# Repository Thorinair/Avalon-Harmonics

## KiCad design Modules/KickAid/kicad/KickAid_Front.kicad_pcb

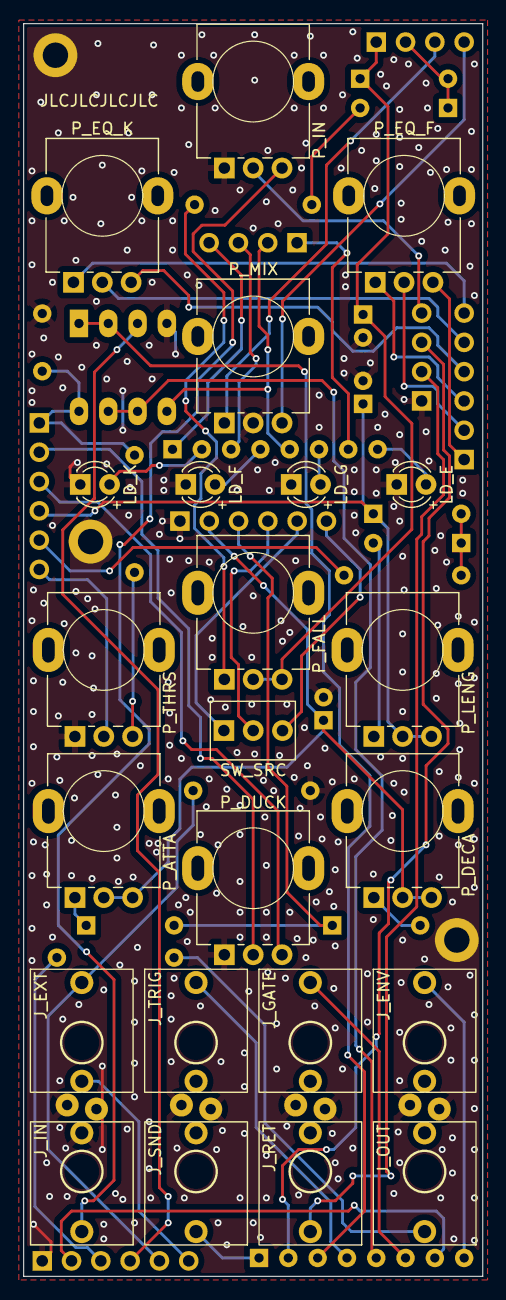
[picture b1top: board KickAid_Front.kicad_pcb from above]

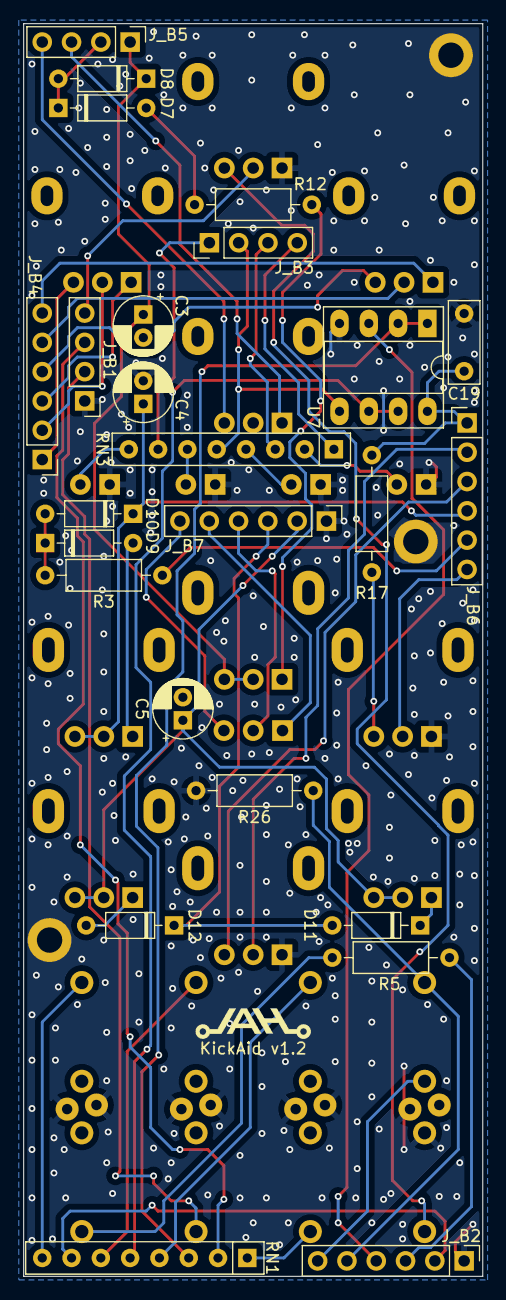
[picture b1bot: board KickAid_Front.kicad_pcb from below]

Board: 2 copper layers, 39.8 x 108.6 mm, 48 parts (25 on the bottom side), 53 nets.

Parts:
C3, C4, C5: 10uF; CP_Radial_D5.0mm_P2.00mm
C19: 0.1uF; C_Disc_D7.0mm_W2.5mm_P5.00mm
D7, D8, D9, D10, D11, D12: 1N4148; D_DO-35_SOD27_P7.62mm_Horizontal
J_B1, J_B3, J_B5: Conn_01x04_Female; PinHeader_1x04_P2.54mm_Vertical
J_B2, J_B4, J_B6, J_B7: Conn_01x06_Female; PinHeader_1x06_P2.54mm_Vertical
J_ENV: PJ301M-12; PJ301M-12 Offset
J_EXT: PJ301M-12; PJ301M-12 Offset
J_GATE: PJ301M-12; PJ301M-12 Offset
J_IN: PJ301M-12; PJ301M-12 Offset
J_OUT: PJ301M-12; PJ301M-12 Offset
J_RET: PJ301M-12; PJ301M-12 Offset
J_SND: PJ301M-12; PJ301M-12 Offset
J_TRIG: PJ301M-12; PJ301M-12 Offset
LD_E: LED; LED_D3.0mm_FlatTop
LD_F: LED; LED_D3.0mm_FlatTop
LD_G: LED; LED_D3.0mm_FlatTop
LD_K: LED; LED_D3.0mm_FlatTop
P_ATTA: A25k; Potentiometer Song Huei 9mm Trimmer
P_DECA: A250k; Potentiometer Song Huei 9mm Trimmer
P_DUCK: B100k; Potentiometer Song Huei 9mm Trimmer
P_EQ_F: B100k; Potentiometer Alpha RD901F-40-00D
P_EQ_K: B100k; Potentiometer Alpha RD901F-40-00D
P_FALL: A1M; Potentiometer Song Huei 9mm Trimmer
P_IN: A100k; Potentiometer Alpha RD901F-40-00D
P_LENG: A100k; Potentiometer Song Huei 9mm Trimmer
P_MIX: B100k; Potentiometer Alpha RD901F-40-00D
P_THRS: B100k; Potentiometer Song Huei 9mm Trimmer
R3: 220; R_Axial_DIN0207_L6.3mm_D2.5mm_P10.16mm_Horizontal
R5: 1k; R_Axial_DIN0207_L6.3mm_D2.5mm_P10.16mm_Horizontal
R12: 10k; R_Axial_DIN0207_L6.3mm_D2.5mm_P10.16mm_Horizontal
R17: 33k; R_Axial_DIN0207_L6.3mm_D2.5mm_P10.16mm_Horizontal
R26: 100k; R_Axial_DIN0207_L6.3mm_D2.5mm_P10.16mm_Horizontal
RN1: 1k; R_Array_SIP8
RN3: 10k; R_Array_SIP8
SW_SRC: SW_SPDT; SPDT
U7: LM358; DIP-8_W7.62mm_Socket_LongPads

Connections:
+12V: C19.1, J_B6.1, R17.1, U7.8 (V+)
/GATE_O1: J_B3.2, RN3.5 (R3.1), U7.5 (+)
/GATE_O2: RN1.5 (R3.1), U7.6 (-), U7.7
/OUT: J_B2.3, R5.2
/TRIG_O1: J_B2.4, U7.3 (+)
/TRIG_O2: RN1.3 (R2.1), U7.1, U7.2 (-)
GND: C3.2, C4.2, C5.2, C19.2, J_B1.1, J_B2.1, J_B7.1, J_ENV.GND, J_EXT.GND, J_GATE.GND, J_IN.GND, J_IN.SW, J_OUT.GND, J_RET.GND, J_SND.GND, J_TRIG.GND, LD_E.1 (K), LD_F.1 (K), LD_G.1 (K), LD_K.1 (K), P_DUCK.1, P_IN.1, P_MIX.2, P_THRS.1, R26.2, U7.4 (V-)
unnamed: D7.2 (A), R12.2
unnamed: D7.1 (K), D8.2 (A), J_B5.2
unnamed: C3.1, D8.1 (K), J_B5.1, P_FALL.2, P_FALL.3
unnamed: D9.2 (A), P_LENG.1
unnamed: D9.1 (K), D10.2 (A), R3.1
unnamed: C4.1, D10.1 (K), J_B6.4, P_LENG.2, P_LENG.3
unnamed: D11.2 (A), D12.1 (K), J_B7.3
unnamed: D11.1 (K), P_ATTA.1
unnamed: D12.2 (A), P_DECA.1
unnamed: J_B1.2, J_RET.SIG
unnamed: J_B1.3, RN1.2 (R1.2)
unnamed: J_B1.4, P_IN.2
unnamed: J_B2.2, RN1.7 (R4.1)
unnamed: J_B2.5, J_EXT.SIG, R26.1
unnamed: J_B2.6, J_EXT.SW
unnamed: J_B3.1, RN3.7 (R4.1)
unnamed: J_B3.3, RN3.3 (R2.1)
unnamed: J_B3.4, RN3.1 (R1.1)
unnamed: J_B4.1, P_EQ_F.3
unnamed: J_B4.2, P_EQ_F.2
unnamed: J_B4.3, P_EQ_F.1
unnamed: J_B4.4, P_EQ_K.3
unnamed: J_B4.5, P_EQ_K.2
unnamed: J_B4.6, P_EQ_K.1
unnamed: J_B5.3, P_MIX.1
unnamed: J_B5.4, P_MIX.3
unnamed: J_B6.2, P_DUCK.2
unnamed: J_B6.3, P_DUCK.3
unnamed: J_B6.5, R3.2
unnamed: J_B6.6, P_THRS.2
unnamed: C5.1, J_B7.2, P_ATTA.2, P_ATTA.3, P_DECA.2, P_DECA.3
unnamed: J_B7.4, SW_SRC.2 (B)
unnamed: J_B7.5, SW_SRC.1 (A)
unnamed: J_B7.6, SW_SRC.3 (C)
unnamed: J_IN.SIG, P_IN.3
unnamed: J_OUT.SIG, R5.1
unnamed: LD_E.2 (A), RN3.8 (R4.2)
unnamed: LD_F.2 (A), RN3.4 (R2.2)
unnamed: LD_G.2 (A), RN3.6 (R3.2)
unnamed: LD_K.2 (A), RN3.2 (R1.2)
unnamed: P_FALL.1, R12.1
unnamed: P_THRS.3, R17.2
unnamed: J_SND.SIG, RN1.1 (R1.1)
unnamed: J_TRIG.SIG, RN1.4 (R2.2)
unnamed: J_GATE.SIG, RN1.6 (R3.2)
unnamed: J_ENV.SIG, RN1.8 (R4.2)

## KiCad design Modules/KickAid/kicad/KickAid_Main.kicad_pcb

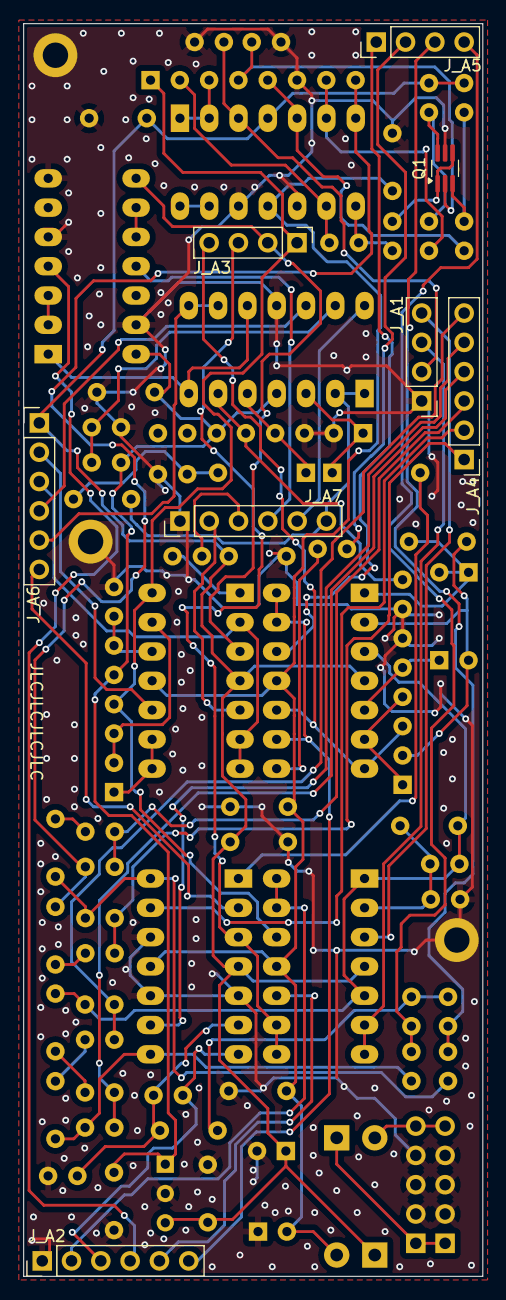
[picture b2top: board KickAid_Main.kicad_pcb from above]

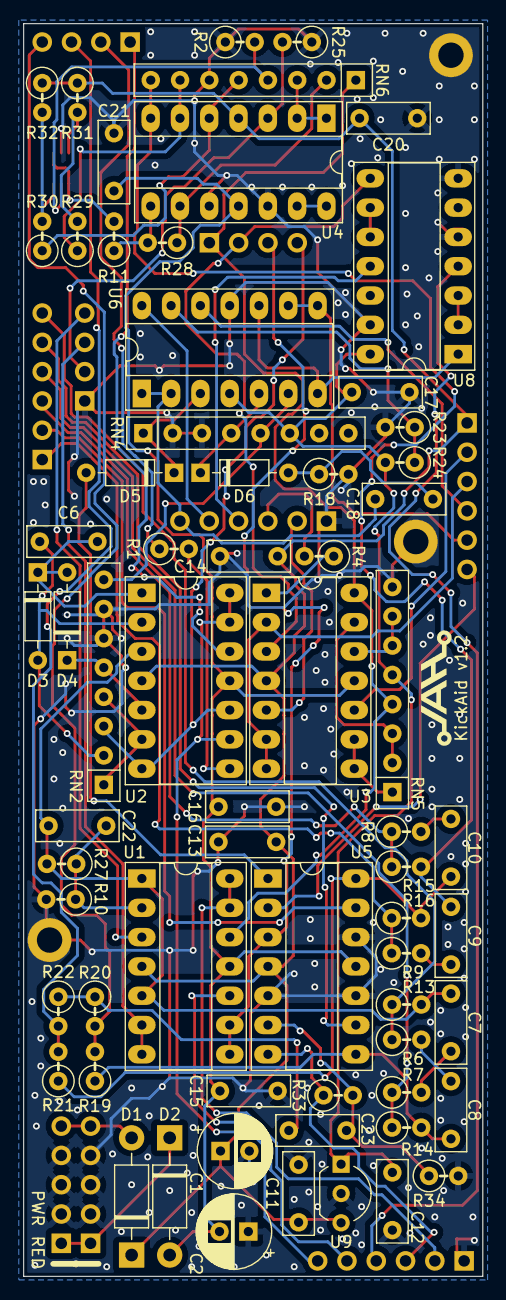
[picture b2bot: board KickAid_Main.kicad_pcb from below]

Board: 2 copper layers, 39.8 x 108.6 mm, 75 parts (67 on the bottom side), 77 nets.

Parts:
C1, C2: 47uF; CP_Radial_D6.3mm_P2.50mm
C6, C22: 47pF; C_Disc_D7.0mm_W2.5mm_P5.00mm
C7, C8, C9, C10, C11, C12, C13, C14, C15, C16, C17, C18, C20, C21, C23: 0.1uF; C_Disc_D7.0mm_W2.5mm_P5.00mm
D1, D2: 1N4001; D_DO-41_SOD81_P10.16mm_Horizontal
D3, D4, D5, D6: 1N4148; D_DO-35_SOD27_P7.62mm_Horizontal
J_A1, J_A3, J_A5: Conn_01x04_Male; PinHeader_1x04_P2.54mm_Vertical
J_A2, J_A4, J_A6, J_A7: Conn_01x06_Male; PinHeader_1x06_P2.54mm_Vertical
PWR1: PWR_10_Pin; Eurorack Power 10 Pin
Q1: BCM847BS; SOT-363_SC-70-6_Handsoldering
R1: 1k; R_Axial_DIN0207_L6.3mm_D2.5mm_P2.54mm_Vertical
R2: 100; R_Axial_DIN0207_L6.3mm_D2.5mm_P2.54mm_Vertical
R4: 330; R_Axial_DIN0207_L6.3mm_D2.5mm_P2.54mm_Vertical
R6, R7, R8, R9: 2.2k; R_Axial_DIN0207_L6.3mm_D2.5mm_P2.54mm_Vertical
R10, R13, R14, R15, R16: 15k; R_Axial_DIN0207_L6.3mm_D2.5mm_P2.54mm_Vertical
R11: 10k; R_Axial_DIN0207_L6.3mm_D2.5mm_P2.54mm_Vertical
R18, R19, R20, R21, R22, R23: 47k; R_Axial_DIN0207_L6.3mm_D2.5mm_P2.54mm_Vertical
R24, R25, R33: 100k; R_Axial_DIN0207_L6.3mm_D2.5mm_P2.54mm_Vertical
R27: 120k; R_Axial_DIN0207_L6.3mm_D2.5mm_P2.54mm_Vertical
R28: 160k; R_Axial_DIN0207_L6.3mm_D2.5mm_P2.54mm_Vertical
R29, R30: 10k 1%; R_Axial_DIN0207_L6.3mm_D2.5mm_P2.54mm_Vertical
R31, R32: 20k 0.1%; R_Axial_DIN0207_L6.3mm_D2.5mm_P2.54mm_Vertical
R34: 240k; R_Axial_DIN0207_L6.3mm_D2.5mm_P2.54mm_Vertical
RN2: 10k; R_Array_SIP8
RN4, RN5, RN6: 100k; R_Array_SIP8
U1, U2, U3, U4, U5: TL074; DIP-14_W7.62mm_Socket_LongPads
U6: LM324; DIP-14_W7.62mm_Socket_LongPads
U8: 74HC04; DIP-14_W7.62mm_Socket_LongPads
U9: 78L05; TO-92_Inline_Wide

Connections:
+5V: C12.1, C17.1, R24.2, RN4.6 (R3.2), RN5.5 (R3.1), U6.4 (V+), U8.14 (VCC), U9.1 (VO)
+12V: C1.1, C11.1, C13.2, C14.2, C20.2, D1.1 (K), J_A6.1, R31.1, R32.1, U1.4 (V+), U2.4 (V+), U3.4 (V+), U4.4 (V+), U5.4 (V+), U9.3 (VI)
-12V: C2.2, C15.1, C16.1, C21.1, D2.2 (A), U1.11 (V-), U2.11 (V-), U3.11 (V-), U4.11 (V-), U5.11 (V-)
/ENV: J_A3.1, RN5.4 (R2.2), RN6.1 (R1.1), U1.12 (+), U3.14
/ENV_R: J_A6.2, U3.10 (+)
/ENV_S: J_A6.3, U3.2 (-), U3.6 (-), U3.7
/EQ_F1: J_A4.3, R8.1, R15.1
/EQ_F2: J_A4.2, U5.13 (-)
/EQ_F3: J_A4.1, R9.1, R16.1
/EQ_K1: J_A4.6, R6.1, R13.1
/EQ_K2: J_A4.5, U5.9 (-)
/EQ_K3: J_A4.4, R7.1, R14.1
/FALL_R: J_A5.1, U2.12 (+)
/FALL_S: J_A5.2, R1.1
/FLWR: J_A3.3, U1.8, U1.9 (-), U5.3 (+)
/FLWR_S: J_A2.6, U2.9 (-), U2.13 (-), U2.14
/FX: C9.1, R15.2, RN6.8 (R4.2), U4.7
/FX_EQ: C10.2, R16.2, R21.1, U5.14
/GATE: J_A3.2, U3.3 (+), U8.8
/GATE_A: C18.1, J_A7.6, U6.1, U6.2 (-)
/GATE_B: J_A7.5, U6.14
/GATE_R: J_A6.4, U6.12 (+)
/GATE_S: J_A6.5, U6.8, U6.9 (-)
/GATE_SW: J_A7.4, U8.11
/KICK: C7.1, C22.2, R13.2, R27.2, U1.1, U1.5 (+), U2.3 (+)
/KICK_EQ: C8.2, R14.2, R19.1, U5.8
/MIX_F: J_A5.3, R21.2, R22.2
/MIX_K: J_A5.4, R19.2, R20.2
/OUT: J_A2.3, R33.1, U5.7
/RECT: J_A3.4, RN2.3 (R2.1), U2.7, U2.10 (+)
/RET: J_A1.2, R25.2, U4.3 (+)
/SEND: J_A1.3, U1.6 (-), U1.7
/SLEW_R: J_A7.2, U3.5 (+)
/SLEW_S: J_A7.3, R4.2
/THRS: J_A6.6, U5.2 (-)
/TRIG: U6.7, U6.10 (+), U8.1
GND: C1.2, C2.1, C11.2, C12.2, C13.1, C14.1, C15.2, C16.2, C17.2, C20.1, C21.2, J_A1.1, J_A2.1, J_A7.1, PWR1.2 (GND), Q1.5 (B2), R2.1, R10.2, R18.2, R23.2, R25.1, R34.2, RN2.6 (R3.2), RN2.7 (R4.1), RN4.2 (R1.2), RN4.3 (R2.1), RN5.8 (R4.2), RN6.6 (R3.2), U4.10 (+), U4.12 (+), U5.5 (+), U5.10 (+), U5.12 (+), U6.11 (V-), U8.5, U8.7 (GND), U8.13, U9.2 (GND)
unnamed: C7.2, R7.2
unnamed: C8.1, R6.2
unnamed: C9.2, R9.2
unnamed: C10.1, R8.2
unnamed: C23.1, R20.1, R22.1
unnamed: D1.2 (A), PWR1.1 (+12V)
unnamed: D2.1 (K), PWR1.3 (-12V)
unnamed: C6.1, D3.2 (A), RN2.2 (R1.2), U2.2 (-)
unnamed: C6.2, D3.1 (K), D4.2 (A), U2.1
unnamed: D4.1 (K), RN2.5 (R3.1), U2.5 (+)
unnamed: D5.2 (A), U5.1
unnamed: D5.1 (K), RN4.1 (R1.1), U6.3 (+)
unnamed: C18.2, D6.2 (A), R18.1
unnamed: D6.1 (K), RN4.4 (R2.2), U6.5 (+)
unnamed: J_A1.4, U1.3 (+)
unnamed: J_A2.2, U1.13 (-), U1.14
unnamed: J_A2.4, U8.4
unnamed: J_A2.5, U1.10 (+)
unnamed: Q1.2 (B1), R2.2, RN6.4 (R2.2)
unnamed: Q1.6 (C1), R29.2, R31.2
unnamed: Q1.1 (E1), Q1.4 (E2), R11.2
unnamed: Q1.3 (C2), R30.2, R32.2
unnamed: R1.2, U2.8
unnamed: R4.1, U3.1
unnamed: R11.1, R28.2, U4.8
unnamed: RN2.1 (R1.1), RN2.4 (R2.2), U2.6 (-)
unnamed: RN2.8 (R4.2), RN4.5 (R3.1), U6.6 (-)
unnamed: RN5.1 (R1.1), U3.8, U3.9 (-)
unnamed: RN5.2 (R1.2), RN5.3 (R2.1), U3.13 (-)
unnamed: RN5.6 (R3.2), RN5.7 (R4.1), U3.12 (+)
unnamed: R28.1, RN6.2 (R1.2), U4.9 (-)
unnamed: RN6.3 (R2.1), U4.1, U4.2 (-)
unnamed: R30.1, RN6.5 (R3.1), U4.5 (+)
unnamed: R29.1, RN6.7 (R4.1), U4.6 (-)
unnamed: C22.1, R10.1, R27.1, U1.2 (-)
unnamed: U4.13 (-), U4.14
unnamed: C23.2, R33.2, R34.1, U5.6 (-)
unnamed: R23.1, R24.1, U6.13 (-)
unnamed: U8.2, U8.3
unnamed: U8.9, U8.10

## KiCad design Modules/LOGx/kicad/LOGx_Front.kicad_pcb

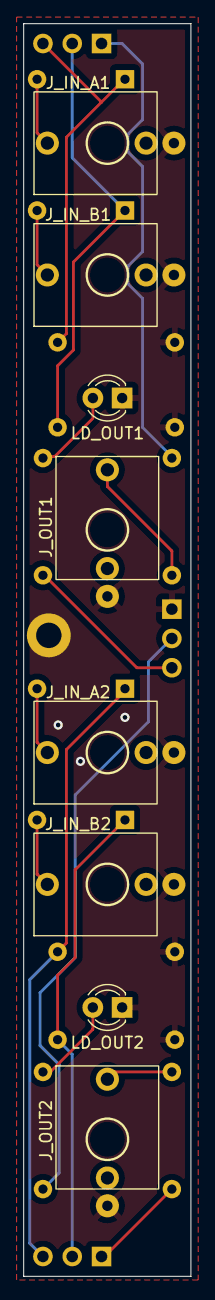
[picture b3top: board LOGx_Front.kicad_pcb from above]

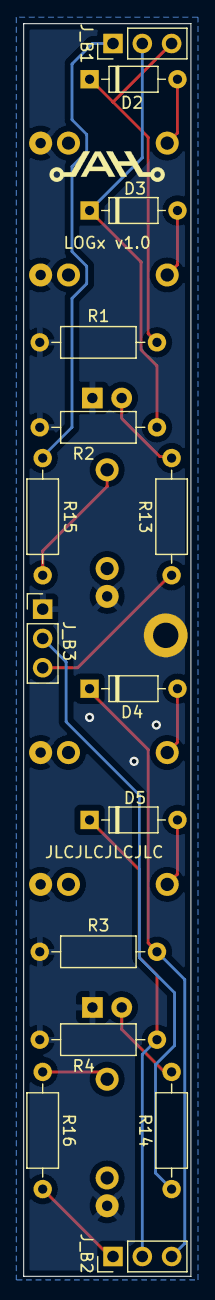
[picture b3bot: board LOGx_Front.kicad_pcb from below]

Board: 2 copper layers, 14.5 x 108.6 mm, 23 parts (15 on the bottom side), 17 nets.

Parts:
D2, D3, D4, D5: 1N4148; D_DO-35_SOD27_P7.62mm_Horizontal
J_B1, J_B2, J_B3: Conn_01x03_Female; PinHeader_1x03_P2.54mm_Vertical
J_IN_A1, J_IN_A2: PJ301M-12
J_IN_B1, J_IN_B2: PJ301M-12
J_OUT1, J_OUT2: PJ301M-12
LD_OUT1, LD_OUT2: LED; LED_D3.0mm_FlatTop
R1, R2, R3, R4: 100k; R_Axial_DIN0207_L6.3mm_D2.5mm_P10.16mm_Horizontal
R13, R14: 10k; R_Axial_DIN0207_L6.3mm_D2.5mm_P10.16mm_Horizontal
R15, R16: 1k; R_Axial_DIN0207_L6.3mm_D2.5mm_P10.16mm_Horizontal

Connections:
GND: J_B3.1, J_IN_A1.GND, J_IN_A2.GND, J_IN_B1.GND, J_IN_B2.GND, J_OUT1.GND, J_OUT2.GND, LD_OUT1.1 (K), LD_OUT2.1 (K), R1.2, R2.2, R3.2, R4.2
unnamed: D2.1 (K), J_B1.3, R1.1
unnamed: D2.2 (A), J_IN_A1.SIG
unnamed: D3.1 (K), J_B1.2, R2.1
unnamed: D3.2 (A), J_IN_B1.SIG
unnamed: D4.1 (K), J_B2.3, R3.1
unnamed: D4.2 (A), J_IN_A2.SIG
unnamed: D5.1 (K), J_B2.2, R4.1
unnamed: D5.2 (A), J_IN_B2.SIG
unnamed: J_B1.1, R15.1
unnamed: J_B2.1, R16.1
unnamed: J_B3.2, R14.1
unnamed: J_B3.3, R13.1
unnamed: J_OUT1.SIG, R15.2
unnamed: J_OUT2.SIG, R16.2
unnamed: LD_OUT1.2 (A), R13.2
unnamed: LD_OUT2.2 (A), R14.2

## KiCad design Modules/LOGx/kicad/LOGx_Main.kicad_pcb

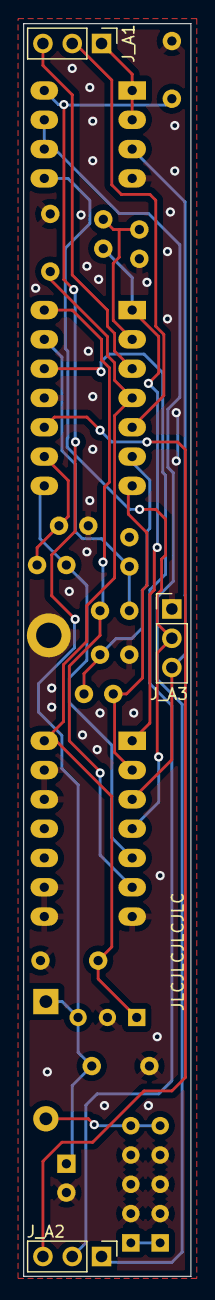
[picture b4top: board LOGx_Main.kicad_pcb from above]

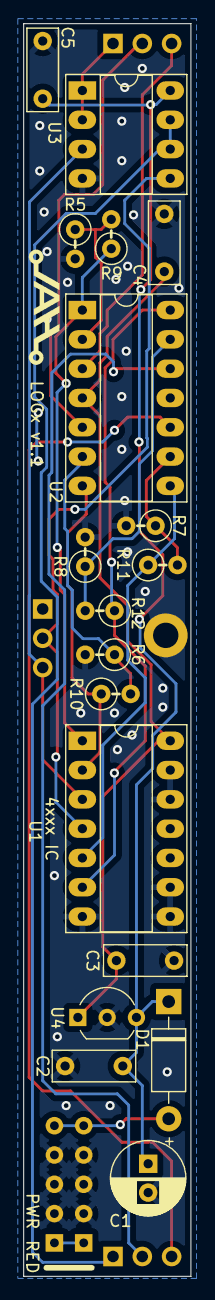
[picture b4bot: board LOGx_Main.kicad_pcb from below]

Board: 2 copper layers, 14.5 x 108.6 mm, 22 parts (19 on the bottom side), 20 nets.

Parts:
C1: 47uF; CP_Radial_D6.3mm_P2.50mm
C2, C3, C4, C5: 0.1uF; C_Disc_D7.0mm_W2.5mm_P5.00mm
D1: 1N4001; D_DO-41_SOD81_P10.16mm_Horizontal
J_A1, J_A2, J_A3: Conn_01x03_Male; PinHeader_1x03_P2.54mm_Vertical
PWR1: PWR_10_Pin; Eurorack Power 10 Pin
R5, R6, R7, R8: 47k; R_Axial_DIN0207_L6.3mm_D2.5mm_P2.54mm_Vertical
R9, R10, R11, R12: 100k; R_Axial_DIN0207_L6.3mm_D2.5mm_P2.54mm_Vertical
U1: 4081; DIP-14_W7.62mm_Socket_LongPads
U2: LM324; DIP-14_W7.62mm_Socket_LongPads
U3: LM358; DIP-8_W7.62mm_Socket_LongPads
U4: 78L05; TO-92_Inline_Wide

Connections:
+5V: C3.1, C4.1, U1.14 (VDD), U2.4 (V+), U4.1 (VO)
+12V: C1.1, C2.1, C5.1, D1.1 (K), U3.8 (V+), U4.3 (VI)
/LED1: J_A3.3, U1.3, U3.3 (+)
/LED2: J_A3.2, U1.4, U3.5 (+)
/OUT1: J_A1.1, U3.1, U3.2 (-)
/OUT2: J_A2.1, U3.6 (-), U3.7
GND: C1.2, C2.2, C3.2, C4.2, C5.2, J_A3.1, PWR1.2 (GND), R5.2, R6.2, R7.2, R8.2, U1.7 (VSS), U1.8, U1.9, U1.12, U1.13, U2.11 (V-), U3.4 (V-), U4.2 (GND)
unnamed: D1.2 (A), PWR1.1 (+12V)
unnamed: J_A1.2, U2.5 (+)
unnamed: J_A1.3, U2.3 (+)
unnamed: J_A2.2, U2.12 (+)
unnamed: J_A2.3, U2.10 (+)
unnamed: R5.1, R9.2, U2.2 (-)
unnamed: R9.1, U1.1, U2.1
unnamed: R10.1, U1.2, U2.7
unnamed: R6.1, R10.2, U2.6 (-)
unnamed: R11.1, U1.5, U2.8
unnamed: R7.1, R11.2, U2.9 (-)
unnamed: R12.1, U1.6, U2.14
unnamed: R8.1, R12.2, U2.13 (-)

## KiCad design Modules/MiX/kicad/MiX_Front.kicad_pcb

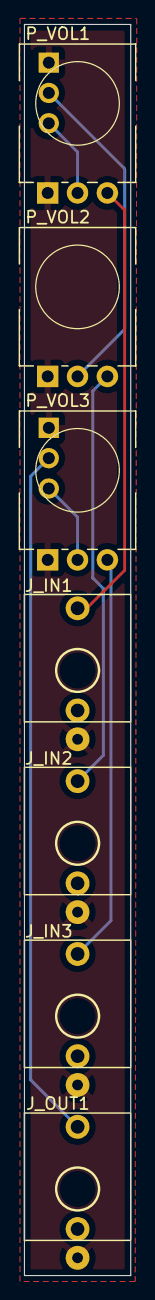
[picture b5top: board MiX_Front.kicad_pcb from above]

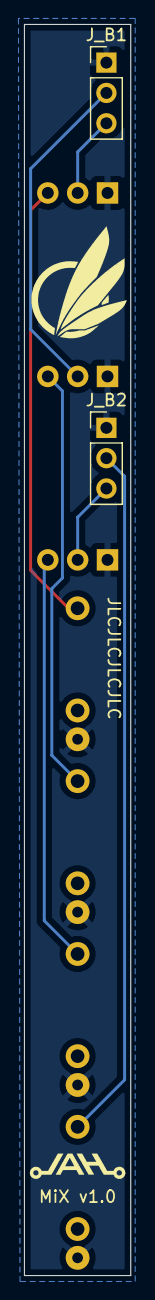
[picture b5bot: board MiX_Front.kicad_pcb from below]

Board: 2 copper layers, 8.9 x 104.8 mm, 9 parts (2 on the bottom side), 8 nets.

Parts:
J_B1, J_B2: Conn_01x03_Female; PinHeader_1x03_P2.54mm_Vertical
J_IN1, J_IN2, J_IN3: PJ301M-12
J_OUT1: PJ301M-12
P_VOL1, P_VOL2, P_VOL3: B100k; Potentiometer Alpha RD901F-40-00D NoSides

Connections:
GND: J_B1.1, J_B2.1, J_IN1.GND, J_IN2.GND, J_IN3.GND, J_OUT1.GND, P_VOL1.1, P_VOL2.1, P_VOL3.1
unnamed: J_IN1.SIG, P_VOL1.3
unnamed: J_IN2.SIG, P_VOL2.3
unnamed: J_IN3.SIG, P_VOL3.3
unnamed: J_B2.2, J_OUT1.SIG
unnamed: J_B1.3, P_VOL1.2
unnamed: J_B1.2, P_VOL2.2
unnamed: J_B2.3, P_VOL3.2

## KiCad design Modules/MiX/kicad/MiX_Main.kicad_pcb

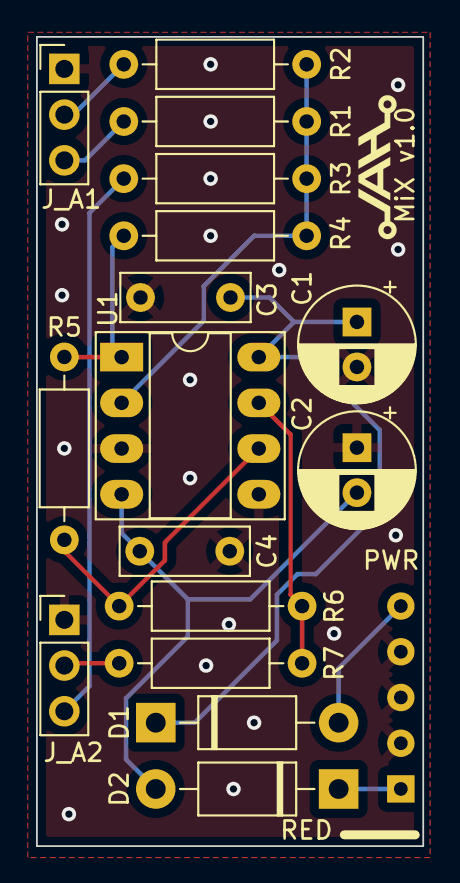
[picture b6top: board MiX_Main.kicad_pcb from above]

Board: 2 copper layers, 21.5 x 45.0 mm, 17 parts (0 on the bottom side), 13 nets.

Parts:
C1, C2: 47uF; CP_Radial_D6.3mm_P2.50mm
C3, C4: 0.1uF; C_Disc_D7.0mm_W2.5mm_P5.00mm
D1, D2: 1N4001; D_DO-41_SOD81_P10.16mm_Horizontal
J_A1, J_A2: Conn_01x03_Male; PinHeader_1x03_P2.54mm_Vertical
PWR1: PWR_5_Pin_Angled; Eurorack Power 5 Pin Angled
R1, R2, R3, R4, R5, R6: 100k; R_Axial_DIN0207_L6.3mm_D2.5mm_P10.16mm_Horizontal
R7: 1k; R_Axial_DIN0207_L6.3mm_D2.5mm_P10.16mm_Horizontal
U1: TL072; DIP-8_W7.62mm_Socket_LongPads

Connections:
+12V: C1.1, C3.1, D1.1 (K), U1.8 (V+)
-12V: C2.2, C4.2, D2.2 (A), U1.4 (V-)
/OUT: J_A2.2, R7.1
GND: C1.2, C2.1, C3.2, C4.1, J_A1.1, J_A2.1, PWR1.2 (GND), U1.3 (+), U1.5 (+)
unnamed: D1.2 (A), PWR1.1 (+12V)
unnamed: D2.1 (K), PWR1.3 (-12V)
unnamed: R1.1, R2.1, R3.1, R4.2, U1.2 (-)
unnamed: J_A1.3, R1.2
unnamed: J_A1.2, R2.2
unnamed: J_A2.3, R3.2
unnamed: R4.1, R5.2, U1.1
unnamed: R5.1, R6.2, U1.6 (-)
unnamed: R6.1, R7.2, U1.7
